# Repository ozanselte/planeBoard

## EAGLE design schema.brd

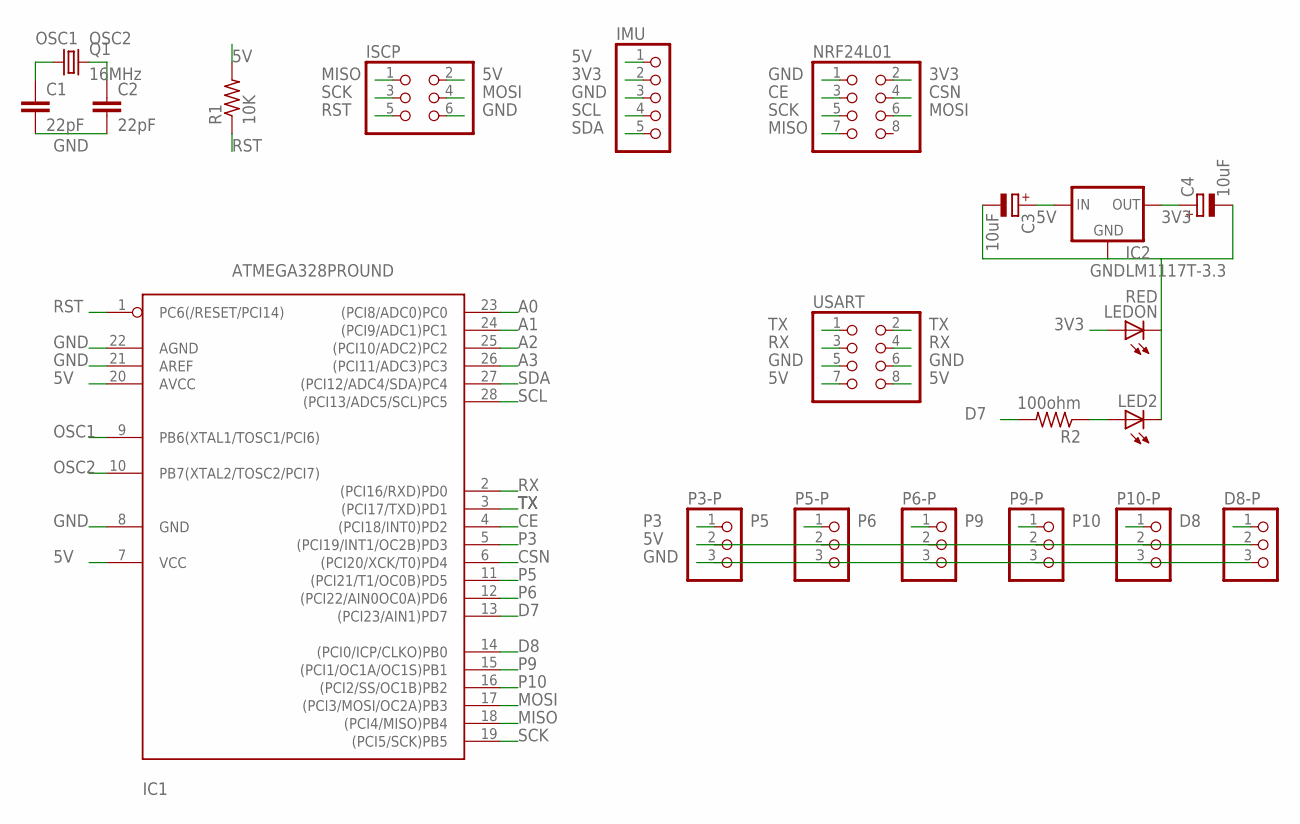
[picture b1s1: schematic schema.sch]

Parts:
C1, C2: 22pF; C025-025X050
C3, C4: 10uF; TT2D5
D8-P: PINHD-1X3; 1X03
IC1: ATMEGA328PROUND; DIL28-3-ROUND
IC2: LM1117T-3.3; TO220
IMU: PINHD-1X5/90; 1X05/90
ISCP: PINHD-2X3; 2X03
LED2: LED3MM
LEDON: RED; LED3MM
NRF24L01: PINHD-2X4/90; 2X04/90
P3-P, P5-P, P6-P, P9-P, P10-P: PINHD-1X3; 1X03
Q1: 16MHz; HC49U70
R1: 10K; 0207/12
R2: 100ohm; 0207/12
USART: PINHD-2X4; 2X04

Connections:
3V3: C4.+, IC2.2 (OUT), IMU.2, LEDON.A, NRF24L01.2
5V: C3.+, D8-P.2, IC1.7 (VCC), IC1.20 (AVCC), IC2.3 (IN), IMU.1, ISCP.2, P3-P.2, P5-P.2, P6-P.2, P9-P.2, P10-P.2, R1.2, USART.7, USART.8
A0: IC1.23 ((PCI8/ADC0)PC0)
A1: IC1.24 ((PCI9/ADC1)PC1)
A2: IC1.25 ((PCI10/ADC2)PC2)
A3: IC1.26 ((PCI11/ADC3)PC3)
CE: IC1.4 ((PCI18/INT0)PD2), NRF24L01.3
CSN: IC1.6 ((PCI20/XCK/T0)PD4), NRF24L01.4
D7: IC1.13 ((PCI23/AIN1)PD7), R2.2
D8: D8-P.1, IC1.14 ((PCI0/ICP/CLKO)PB0)
GND: C1.2, C2.2, C3.-, C4.-, D8-P.3, IC1.8 (GND), IC1.21 (AREF), IC1.22 (AGND), IC2.1 (GND), IMU.3, ISCP.6, LED2.K (C), LEDON.K (C), NRF24L01.1, P3-P.3, P5-P.3, P6-P.3, P9-P.3, P10-P.3, USART.5, USART.6
MISO: IC1.18 ((PCI4/MISO)PB4), ISCP.1, NRF24L01.7
MOSI: IC1.17 ((PCI3/MOSI/OC2A)PB3), ISCP.4, NRF24L01.6
unnamed: LED2.A, R2.1
OSC1: C1.1, IC1.9 (PB6(XTAL1/TOSC1/PCI6)), Q1.1
OSC2: C2.1, IC1.10 (PB7(XTAL2/TOSC2/PCI7)), Q1.2
P3: IC1.5 ((PCI19/INT1/OC2B)PD3), P3-P.1
P5: IC1.11 ((PCI21/T1/OC0B)PD5), P5-P.1
P6: IC1.12 ((PCI22/AIN0OC0A)PD6), P6-P.1
P9: IC1.15 ((PCI1/OC1A/OC1S)PB1), P9-P.1
P10: IC1.16 ((PCI2/SS/OC1B)PB2), P10-P.1
RST: IC1.1 (PC6(/RESET/PCI14)), ISCP.5, R1.1
RX: IC1.2 ((PCI16/RXD)PD0), USART.3, USART.4
SCK: IC1.19 ((PCI5/SCK)PB5), ISCP.3, NRF24L01.5
SCL: IC1.28 ((PCI13/ADC5/SCL)PC5), IMU.4
SDA: IC1.27 ((PCI12/ADC4/SDA)PC4), IMU.5
TX: IC1.3 ((PCI17/TXD)PD1), USART.1, USART.2

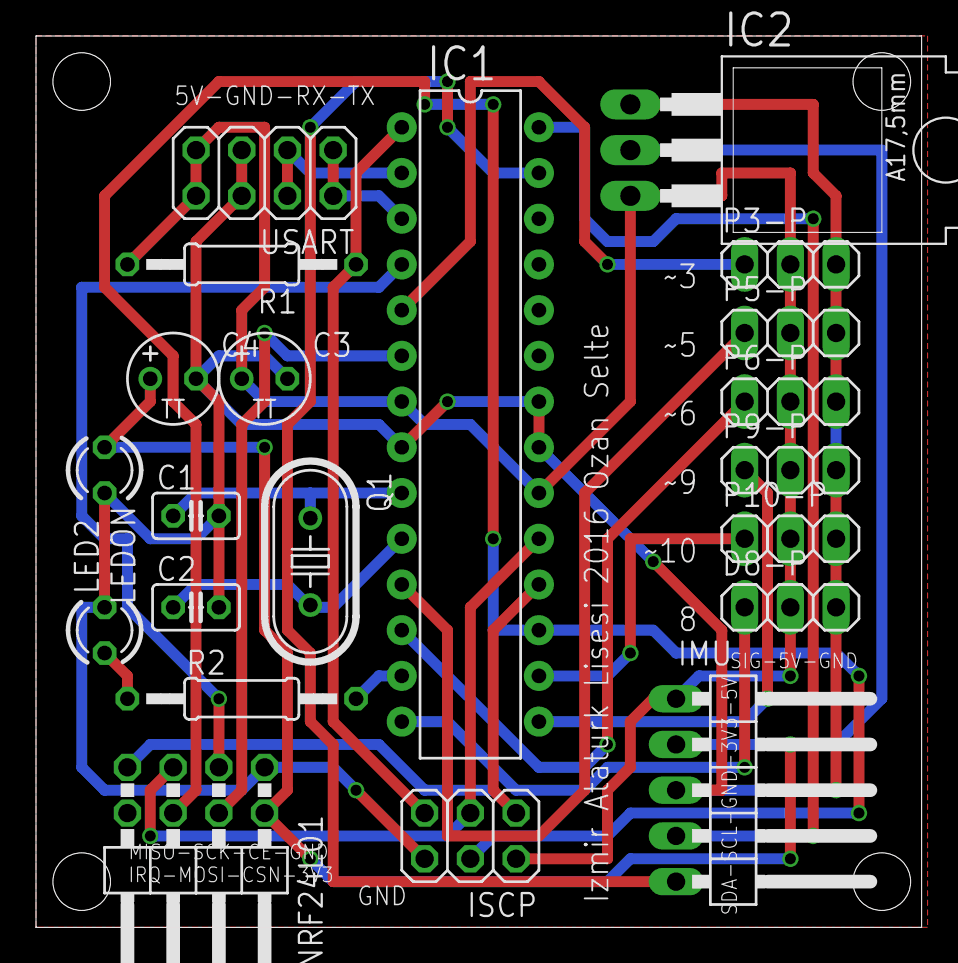
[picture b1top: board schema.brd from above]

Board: 2 copper layers, 49.2 x 49.5 mm, 21 parts (0 on the bottom side), 23 nets.

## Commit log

2016-06-25 v0.0.1
